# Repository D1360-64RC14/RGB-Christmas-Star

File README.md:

# Estrela de Natal Gamer

</img>

Uma estrela de Natal 3D de duas PCBs feita para ser colocada em cima da sua árvore de Natal. Brilhando com ajuda de 40 LEDs RGB [WS2812B](https://br.mouser.com/ProductDetail/Adafruit/4684?qs=sGAEpiMZZMv0NwlthflBi8VlGLu%2FauqZ371fTYmjTRw%3D) para levar os FPS de sua árvore para os céus, e um humilde [ESP-01](https://br.mouser.com/ProductDetail/SparkFun/WRL-17146?qs=sGAEpiMZZMv0NwlthflBi8Gp9XeNVzlnaVzjDrRsb4U%3D) em seu coração para trazer mais felicidade ao seu Natal.

- Suporta uma tensão de 5V a 12V graças aos reguladores de tensão TLV1117;
- A placa Master pode funcionar independentemente da placa Slave;
- LEDs controlados pelo pino GPIO0;
- PCB de 1.2mm a 1.4mm de espessura.

## Lista de Materiais

[Lista de Compras Mouser](https://br.mouser.com/ProjectManager/ProjectDetail.aspx?AccessID=6eb410d618)

| Imagem | Material | Quantidade |
|:------:|:--------:|:----------:|
|</img>|[Adafruit WS2812B](https://br.mouser.com/ProductDetail/Adafruit/4684?qs=sGAEpiMZZMv0NwlthflBi8VlGLu%2FauqZ371fTYmjTRw%3D)|40|
|</img>|[ESP8266 ESP-01](https://br.mouser.com/ProductDetail/SparkFun/WRL-17146?qs=sGAEpiMZZMv0NwlthflBi8Gp9XeNVzlnaVzjDrRsb4U%3D)|1|
|</img>|[Female Header 02x08 2.54mm](https://br.mouser.com/ProductDetail/TE-Connectivity/5-534206-4?qs=Eln3I3szM1ldJZZch%252BwNBQ%3D%3D)|1|
|</img>|[Male Header 01x02 2.54mm Right Angle](https://br.mouser.com/ProductDetail/Amphenol-FCI/68016-202HLF?qs=QKvFUfBIyQII0wp0LUv6XQ%3D%3D)|1|
|</img>|[Voltage Regulator TLV1117-50CDCY](https://br.mouser.com/ProductDetail/Texas-Instruments/TLV1117-50CDCY?qs=p6lVfQR1GSpDSJc9oax3wA%3D%3D)|2|
|</img>|[Voltage Regulator TLV1117-33CDCY](https://br.mouser.com/ProductDetail/Texas-Instruments/TLV1117-33CDCY?qs=p6lVfQR1GSrArgD96KIXHQ%3D%3D)|1|

## Imagens

</img>
</img>
</img>
</img>

#[JuliaLabs](https://twitch.tv/julialabs)PCBChallenge, #XMas2021

---

<br />This work is licensed under a <a rel="license" href="http://creativecommons.org/licenses/by-sa/4.0/">Creative Commons Attribution-ShareAlike 4.0 International License</a>.

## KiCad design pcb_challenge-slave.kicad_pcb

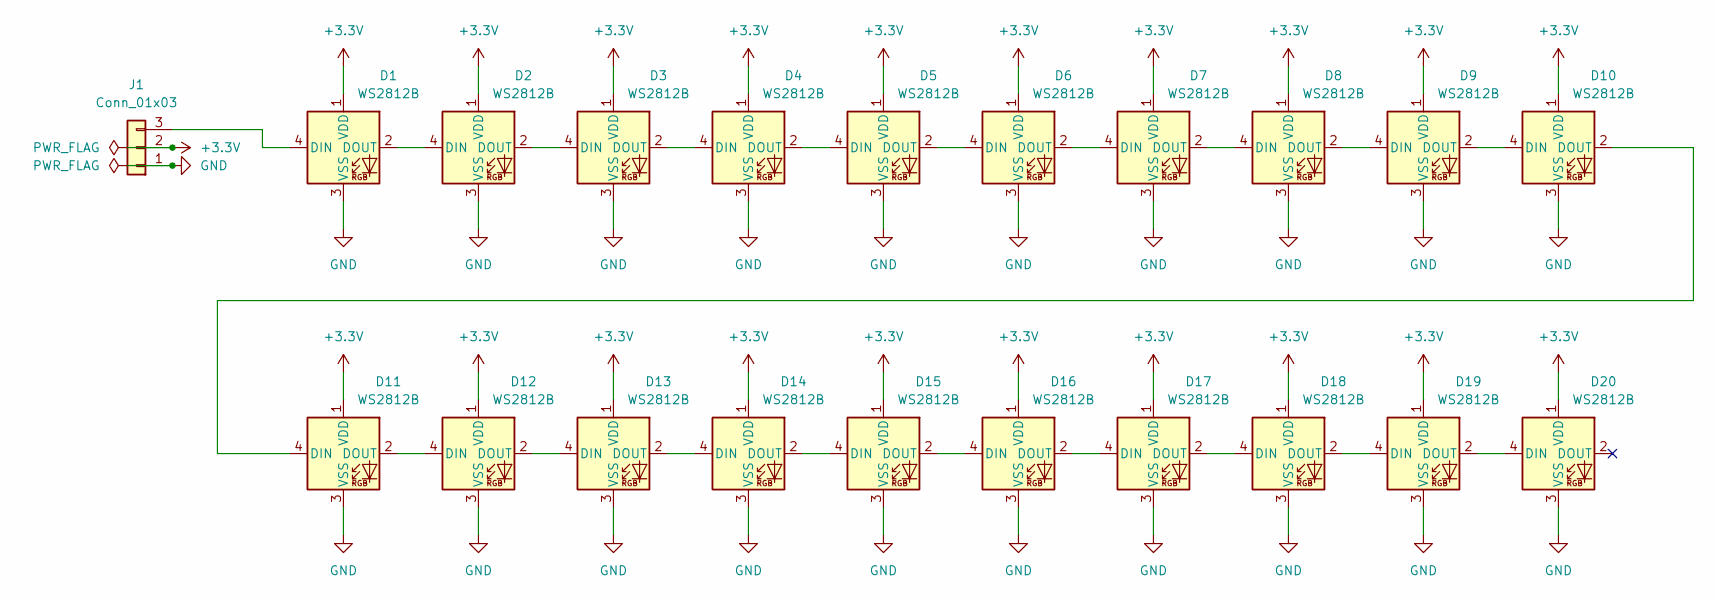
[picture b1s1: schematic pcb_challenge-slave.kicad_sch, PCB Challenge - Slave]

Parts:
D1, D2, D3, D4, D5, D6, D7, D8, D9, D10, D11, D12, D13, D14, D15, D16, D17, D18, D19, D20: WS2812B; LED_WS2812B_PLCC4_5.0x5.0mm_P3.2mm
J1: Conn_01x03; PinHeader_1x03_P2.54mm_Vertical

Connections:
+3V3: D1.1 (VDD), D2.1 (VDD), D3.1 (VDD), D4.1 (VDD), D5.1 (VDD), D6.1 (VDD), D7.1 (VDD), D8.1 (VDD), D9.1 (VDD), D10.1 (VDD), D11.1 (VDD), D12.1 (VDD), D13.1 (VDD), D14.1 (VDD), D15.1 (VDD), D16.1 (VDD), D17.1 (VDD), D18.1 (VDD), D19.1 (VDD), D20.1 (VDD), J1.2
GND: D1.3 (VSS), D2.3 (VSS), D3.3 (VSS), D4.3 (VSS), D5.3 (VSS), D6.3 (VSS), D7.3 (VSS), D8.3 (VSS), D9.3 (VSS), D10.3 (VSS), D11.3 (VSS), D12.3 (VSS), D13.3 (VSS), D14.3 (VSS), D15.3 (VSS), D16.3 (VSS), D17.3 (VSS), D18.3 (VSS), D19.3 (VSS), D20.3 (VSS), J1.1
unnamed: D1.2 (DOUT), D2.4 (DIN)
unnamed: D1.4 (DIN), J1.3
unnamed: D2.2 (DOUT), D3.4 (DIN)
unnamed: D3.2 (DOUT), D4.4 (DIN)
unnamed: D4.2 (DOUT), D5.4 (DIN)
unnamed: D5.2 (DOUT), D6.4 (DIN)
unnamed: D6.2 (DOUT), D7.4 (DIN)
unnamed: D7.2 (DOUT), D8.4 (DIN)
unnamed: D8.2 (DOUT), D9.4 (DIN)
unnamed: D10.2 (DOUT), D11.4 (DIN)
unnamed: D9.2 (DOUT), D10.4 (DIN)
unnamed: D11.2 (DOUT), D12.4 (DIN)
unnamed: D12.2 (DOUT), D13.4 (DIN)
unnamed: D13.2 (DOUT), D14.4 (DIN)
unnamed: D14.2 (DOUT), D15.4 (DIN)
unnamed: D15.2 (DOUT), D16.4 (DIN)
unnamed: D16.2 (DOUT), D17.4 (DIN)
unnamed: D17.2 (DOUT), D18.4 (DIN)
unnamed: D18.2 (DOUT), D19.4 (DIN)
unnamed: D19.2 (DOUT), D20.4 (DIN)

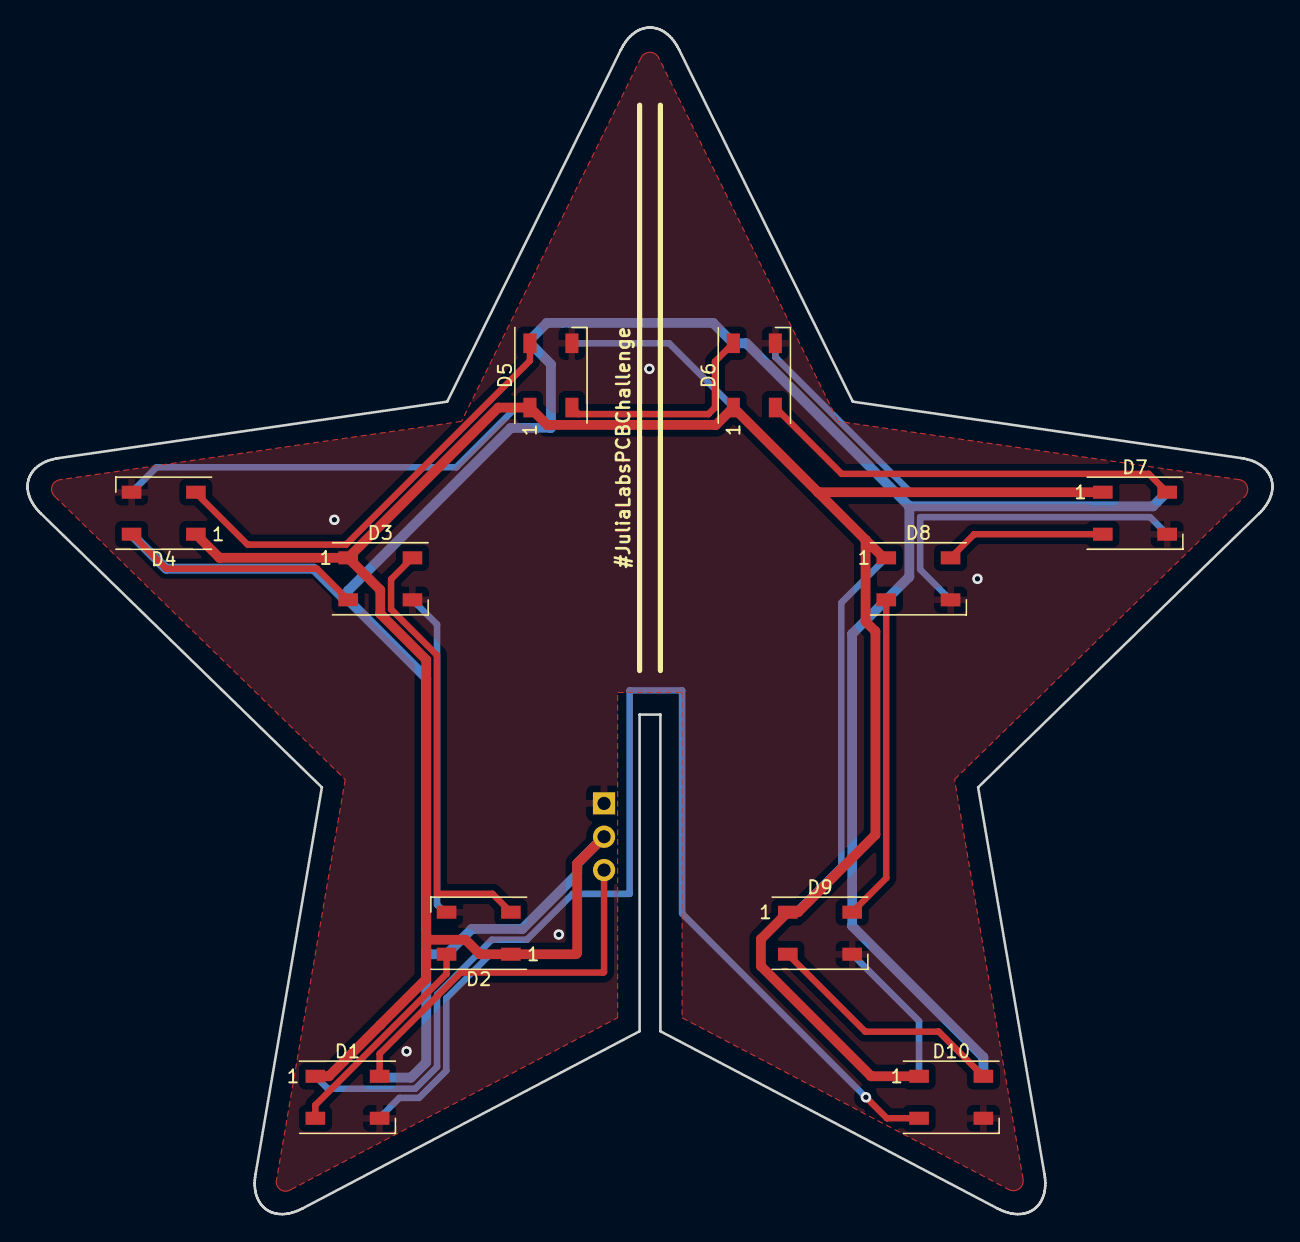
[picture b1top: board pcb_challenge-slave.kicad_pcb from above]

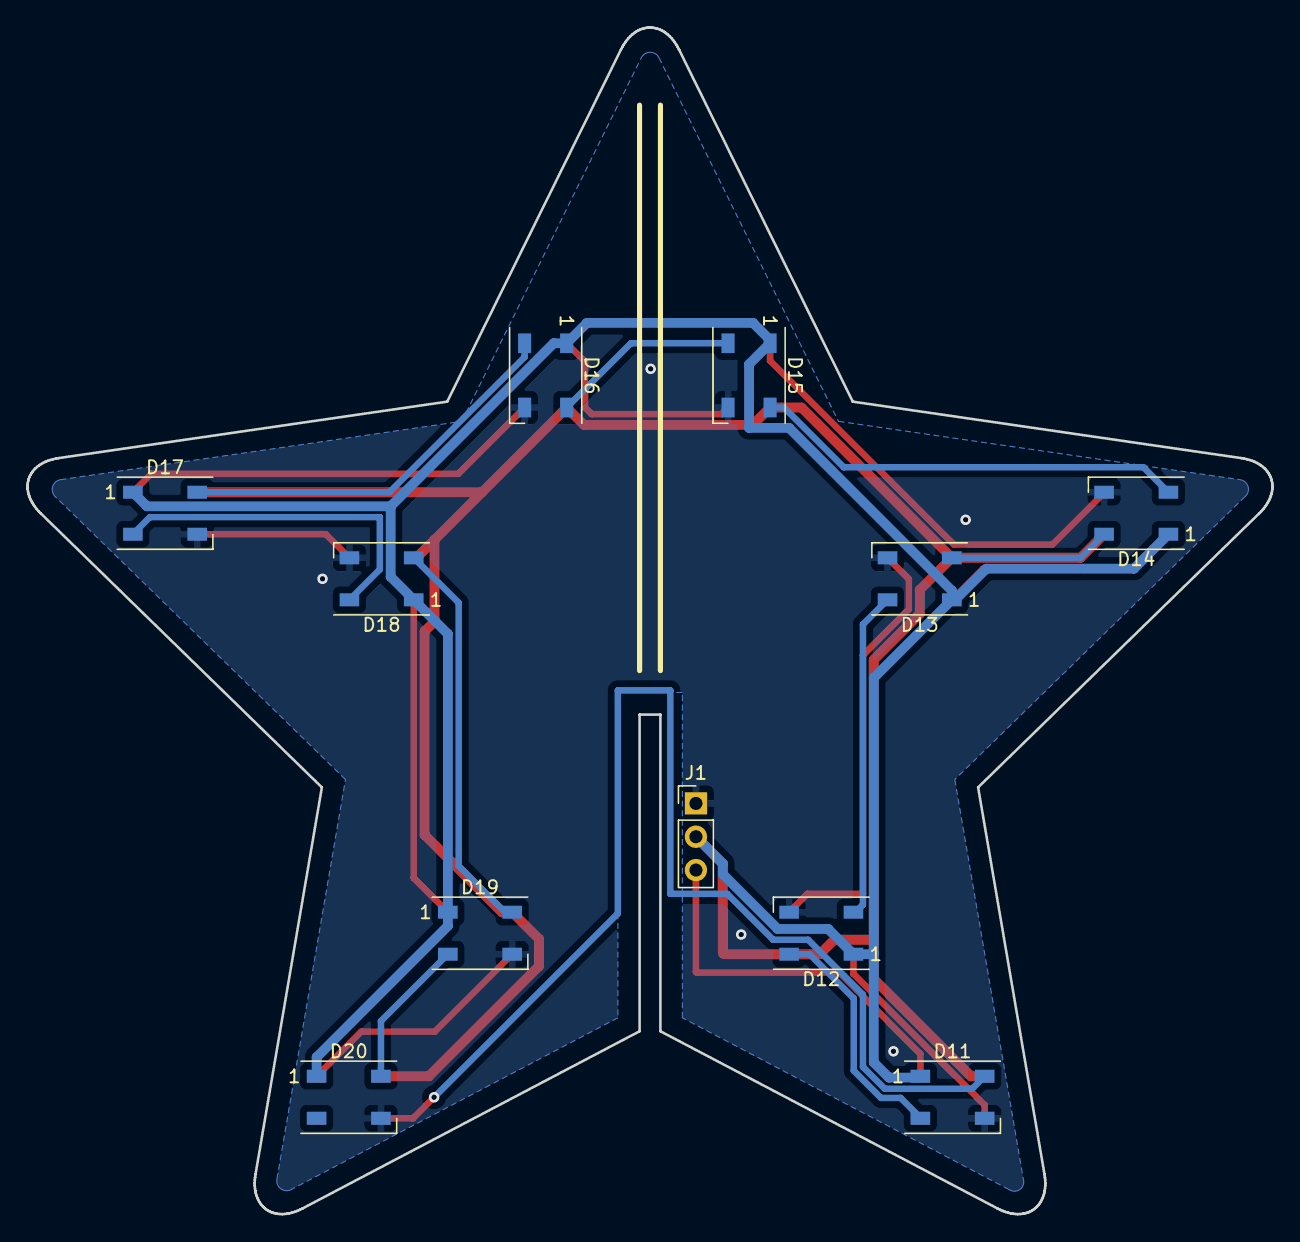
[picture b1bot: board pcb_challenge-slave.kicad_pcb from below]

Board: 2 copper layers, 94.9 x 90.4 mm, 21 parts (11 on the bottom side), 22 nets.

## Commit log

2022-01-14 Project
2022-01-14 Adicionado lista de compras mouser
2022-01-14 Removido imagem duplicada
2022-01-17 Complemento à descrição
